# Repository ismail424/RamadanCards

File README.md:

# Digital Ramadan Cards Project

**By Ismail Sacic**

Welcome to the Digital Ramadan Cards project! This repository contains the design and source files for creating unique, digital printed circuit board (PCB) cards specifically designed for Ramadan.

## Project Overview

I am creating digital Ramadan cards that combine traditional aesthetics with modern electronics. These cards are designed using KiCad and can be manufactured as PCBs. They serve as beautiful, tech-inspired gifts or decorative pieces to celebrate the holy month of Ramadan.

### Features
- **Design Year**: 2026
- **Format**: KiCad PCB Design
- **Custom Graphics**: Includes custom silk screen art (Mosque/Stars).

## Preview

Here are some preview images of the 2026 card design:

## Repository Structure

- `2026/` : Contains the KiCad project files for the 2026 edition.
  - `gr/` : Gerber files for manufacturing.
  - `Graphics/` : Custom footprints and graphics used on the PCB.
  - `preview/` : Images of the design.

## How to Open

1. Install [KiCad](https://www.kicad.org/).
2. Open the `.kicad_pro` file located in the `2026/` directory.

## License

**Copyright © 2026 Ismail Sacic. All Rights Reserved.**

This project is for personal viewing only. **You are not allowed to manufacture, produce, or sell** cards based on this design. See the [LICENSE](LICENSE) file for more details.

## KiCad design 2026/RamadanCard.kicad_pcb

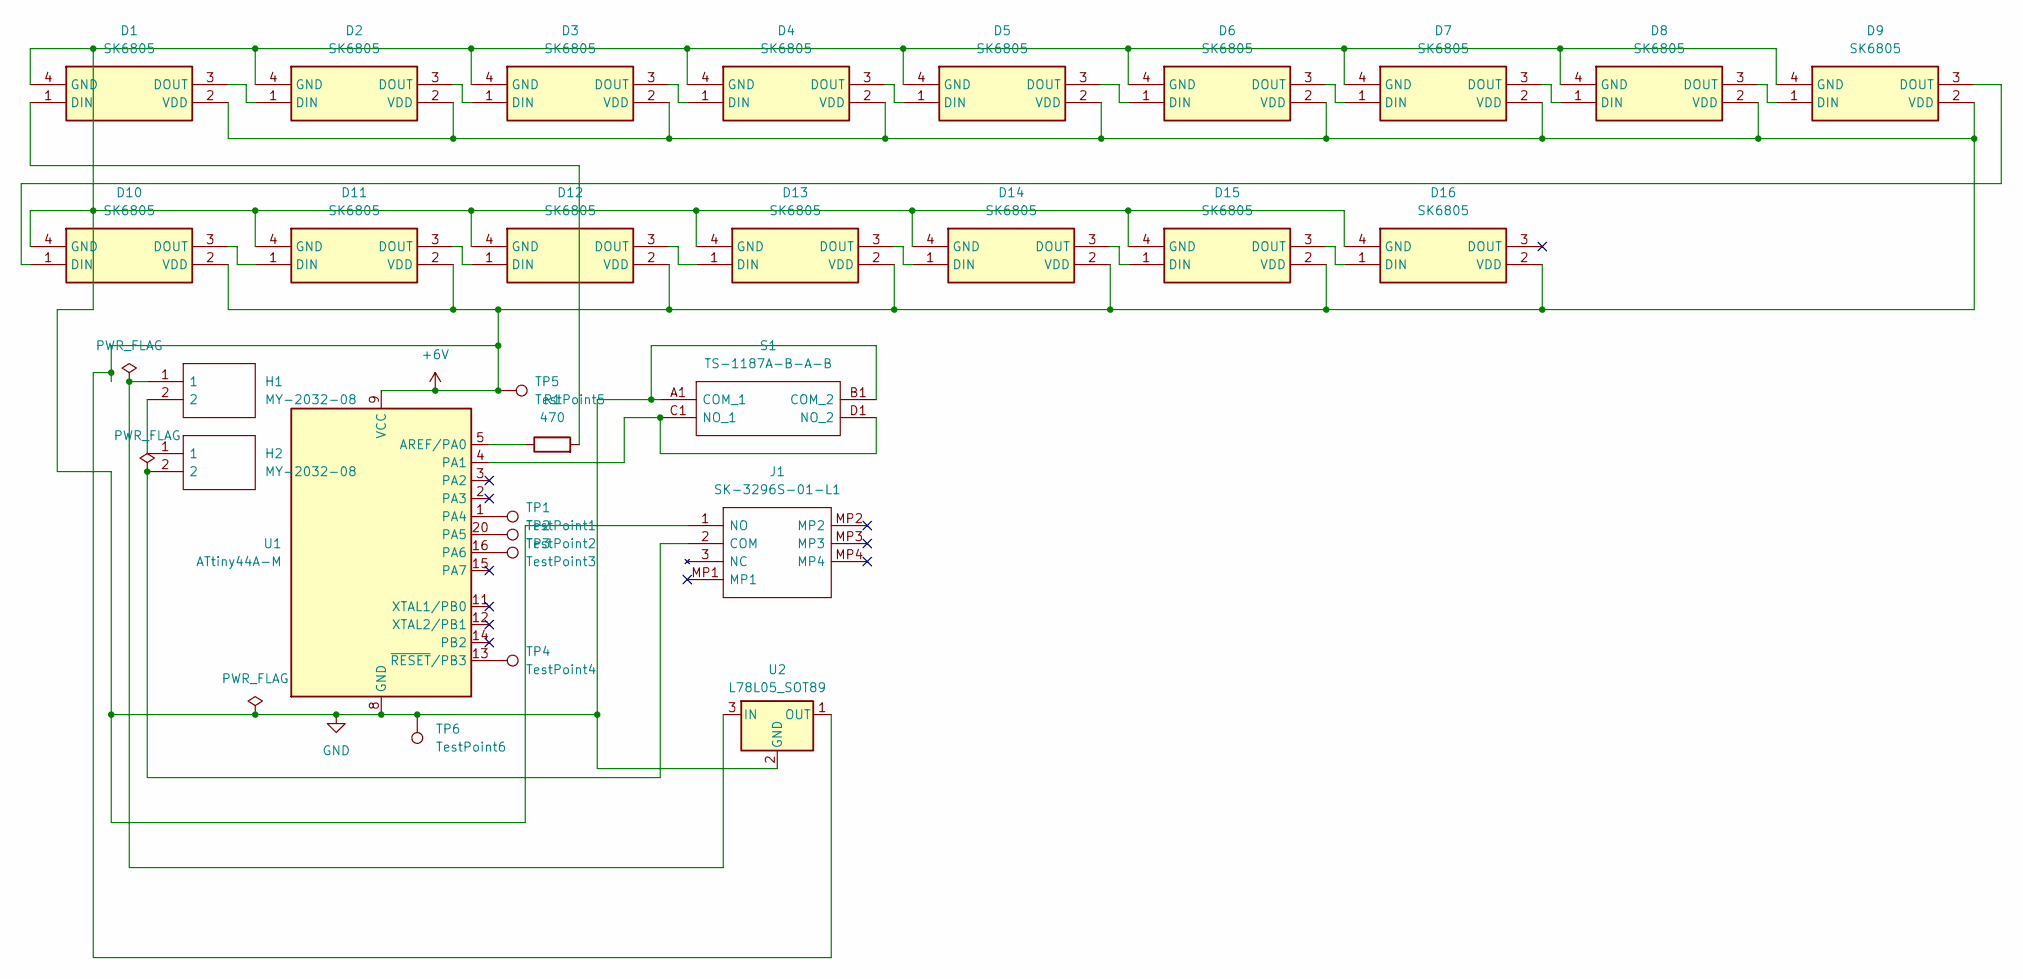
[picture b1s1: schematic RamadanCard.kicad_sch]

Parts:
D1, D2, D3, D4, D5, D6, D7, D8, D9, D10, D11, D12, D13, D14, D15, D16: SK6805; LED_SK6812_EC15_1.5x1.5mm; Manufacturer_Part_Number SK6805-EC15
H1, H2: MY-2032-08; MY203208; Manufacturer_Part_Number MY-2032-08
J1: SK-3296S-01-L1; SK3296S01L1; Manufacturer_Part_Number SK-3296S-01-L1
R1: 470; R_0603_1608Metric
S1: TS-1187A-B-A-B; TS1187ABAB; Manufacturer_Part_Number TS-1187A-B-A-B
TP1: TestPoint1; TestPoint_Pad_D1.5mm
TP2: TestPoint2; TestPoint_Pad_D1.5mm
TP3: TestPoint3; TestPoint_Pad_D1.5mm
TP4: TestPoint4; TestPoint_Pad_D1.5mm
TP5: TestPoint5; TestPoint_Pad_D1.5mm
TP6: TestPoint6; TestPoint_Pad_D1.5mm
U1: ATtiny44A-M; QFN-20-1EP_4x4mm_P0.5mm_EP2.5x2.5mm_ThermalVias
U2: L78L05_SOT89; SOT-89-3

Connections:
+6V: D1.2 (VDD), D2.2 (VDD), D3.2 (VDD), D4.2 (VDD), D5.2 (VDD), D6.2 (VDD), D7.2 (VDD), D8.2 (VDD), D9.2 (VDD), D10.2 (VDD), D11.2 (VDD), D12.2 (VDD), D13.2 (VDD), D14.2 (VDD), D15.2 (VDD), D16.2 (VDD), TP5.1, U1.9 (VCC), U2.1 (OUT)
GND: D1.4 (GND), D2.4 (GND), D3.4 (GND), D4.4 (GND), D5.4 (GND), D6.4 (GND), D7.4 (GND), D8.4 (GND), D9.4 (GND), D10.4 (GND), D11.4 (GND), D12.4 (GND), D13.4 (GND), D14.4 (GND), D15.4 (GND), D16.4 (GND), J1.1 (NO), S1.A1 (COM_1), S1.B1 (COM_2), TP6.1, U1.8 (GND), U1.21 (GND), U2.2 (GND)
unnamed: D1.1 (DIN), R1.2
unnamed: D1.3 (DOUT), D2.1 (DIN)
unnamed: D2.3 (DOUT), D3.1 (DIN)
unnamed: D3.3 (DOUT), D4.1 (DIN)
unnamed: D4.3 (DOUT), D5.1 (DIN)
unnamed: D5.3 (DOUT), D6.1 (DIN)
unnamed: D6.3 (DOUT), D7.1 (DIN)
unnamed: D7.3 (DOUT), D8.1 (DIN)
unnamed: D8.3 (DOUT), D9.1 (DIN)
unnamed: D9.3 (DOUT), D10.1 (DIN)
unnamed: D10.3 (DOUT), D11.1 (DIN)
unnamed: D11.3 (DOUT), D12.1 (DIN)
unnamed: D12.3 (DOUT), D13.1 (DIN)
unnamed: D13.3 (DOUT), D14.1 (DIN)
unnamed: D14.3 (DOUT), D15.1 (DIN)
unnamed: D15.3 (DOUT), D16.1 (DIN)
unnamed: H1.2, H2.1
unnamed: H2.2, J1.2 (COM)
unnamed: S1.C1 (NO_1), S1.D1 (NO_2), U1.4 (PA1)
unnamed: R1.1, U1.5 (AREF/PA0)
unnamed: TP1.1, U1.1 (PA4)
unnamed: TP2.1, U1.20 (PA5)
unnamed: TP3.1, U1.16 (PA6)
unnamed: TP4.1, U1.13 (~RESET/PB3)
unnamed: H1.1, U2.3 (IN)

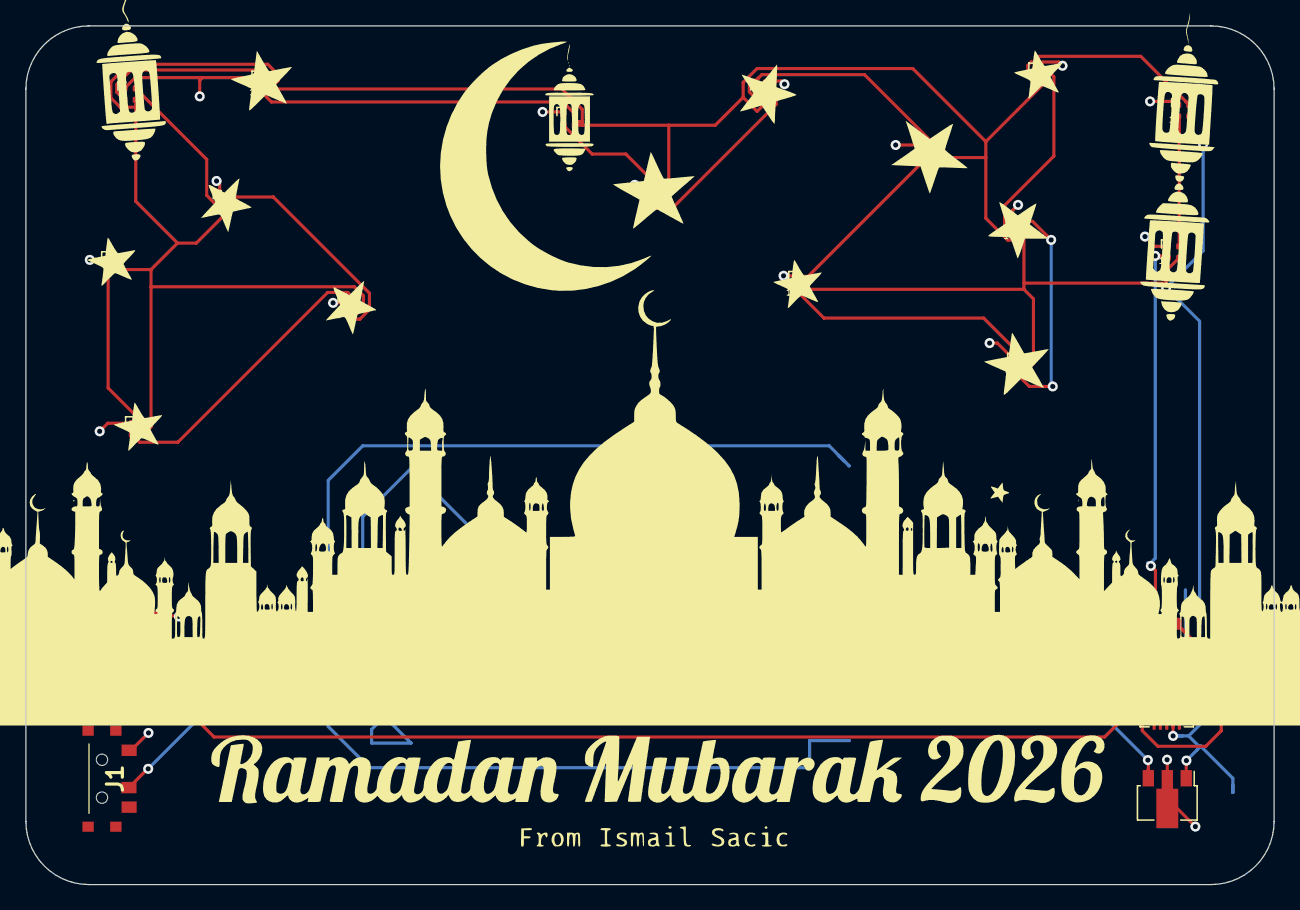
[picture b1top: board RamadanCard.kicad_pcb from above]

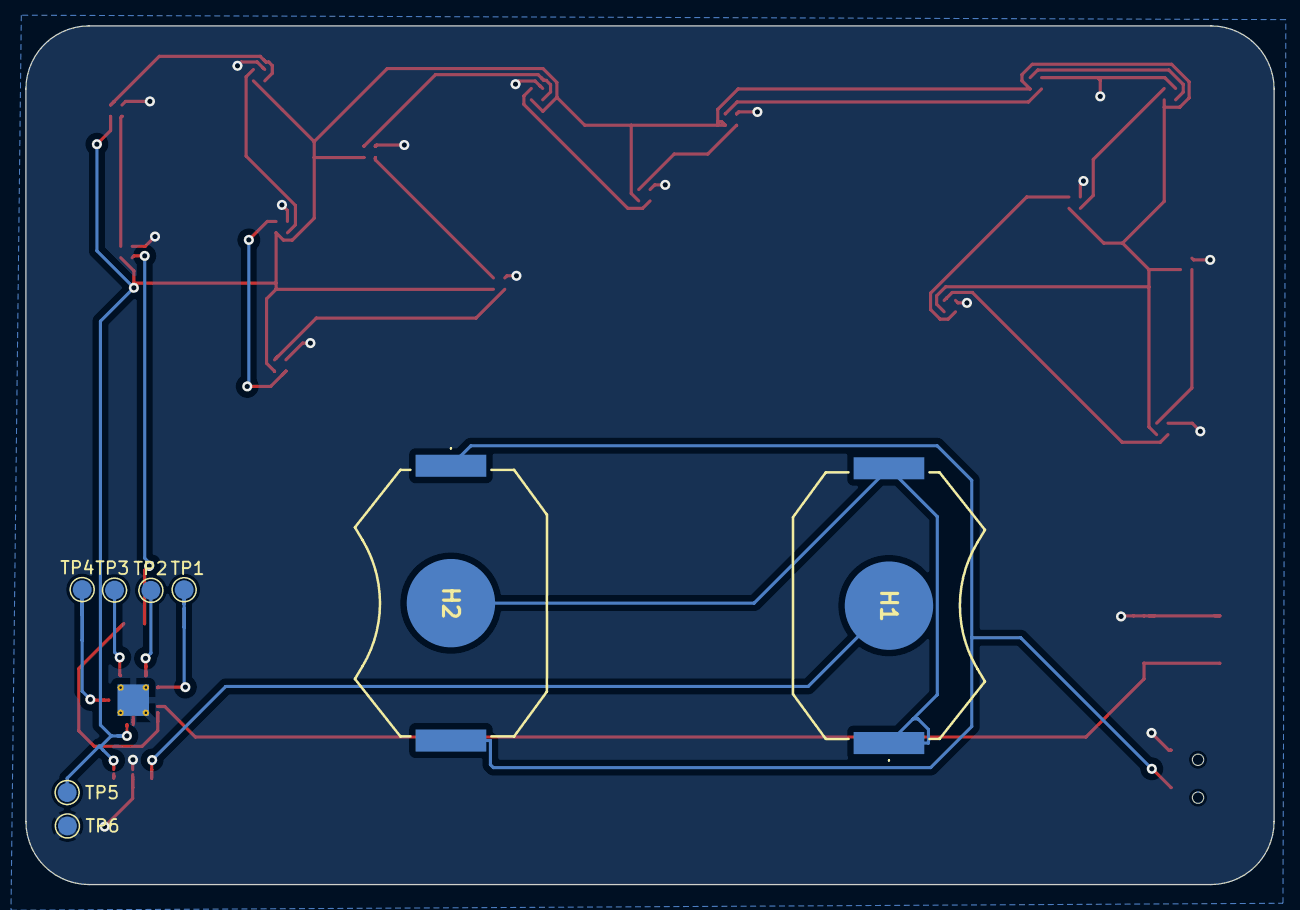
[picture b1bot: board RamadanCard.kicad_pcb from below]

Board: 2 copper layers, 98.8 x 68.0 mm, 29 parts (8 on the bottom side), 27 nets.

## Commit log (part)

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2026-02-24 Add new netlist file for 2026 production with detailed VIA and connection specifications
